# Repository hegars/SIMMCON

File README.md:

# SIMMCON
 
A KiCAD Redraw of the AWE64 SIMMConn Module from https://simmconn.tripod.com/

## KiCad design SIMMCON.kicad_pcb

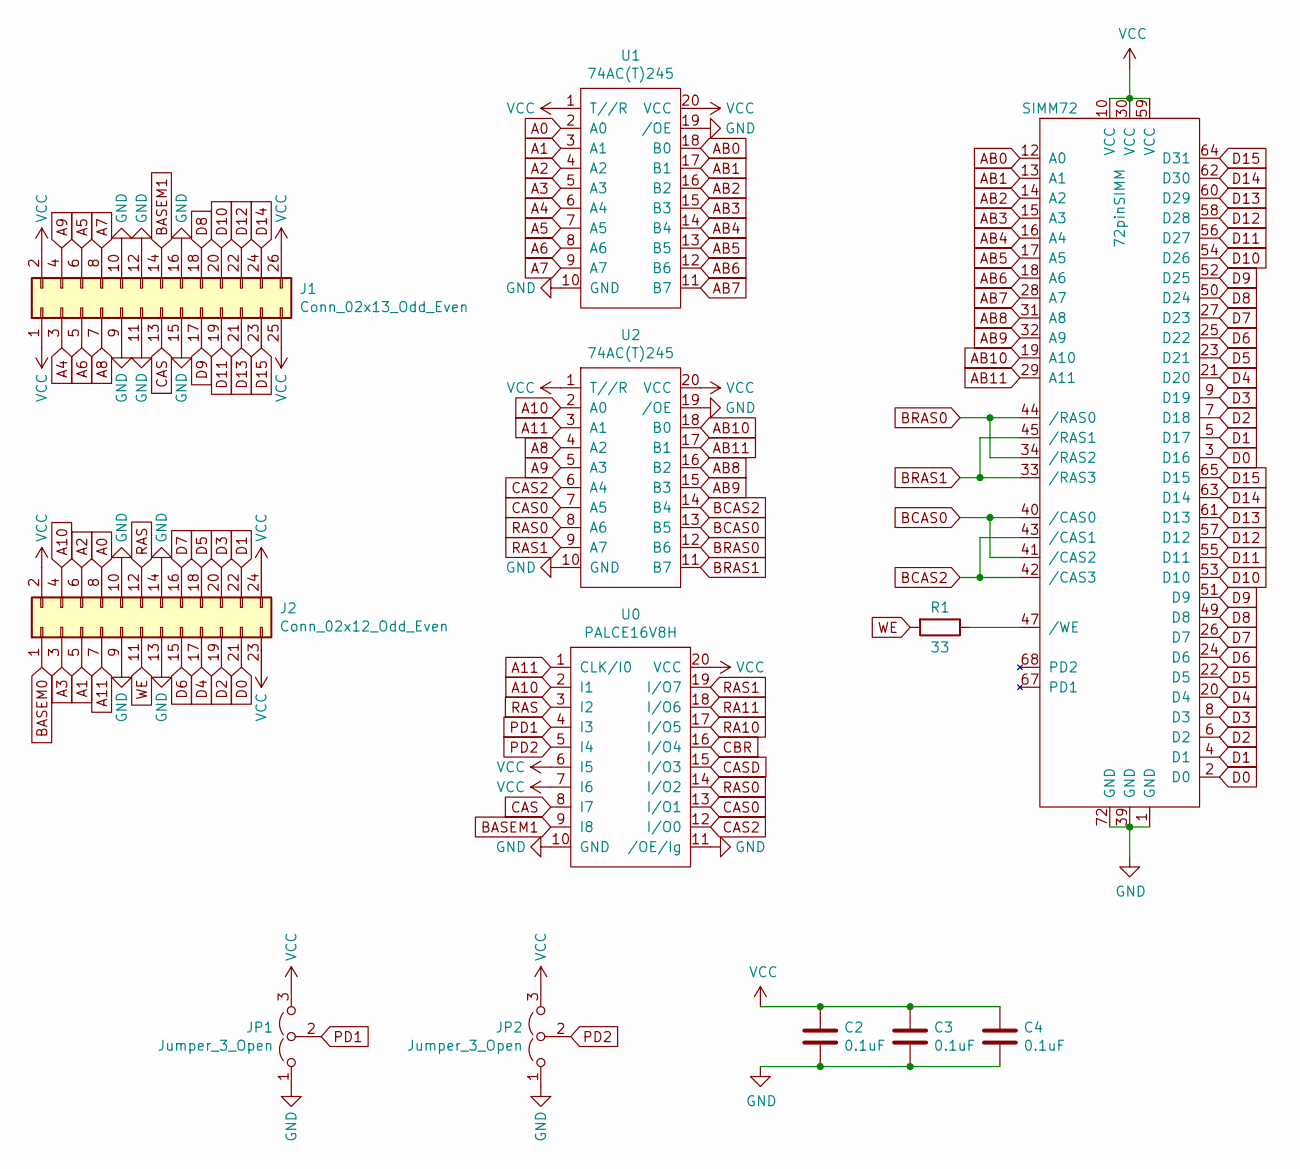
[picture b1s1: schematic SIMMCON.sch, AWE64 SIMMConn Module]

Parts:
C2, C3, C4: 0.1uF; C_0805
J1: Conn_02x13_Odd_Even; Pin_Header_Straight_2x13_Pitch2.00mm
J2: Conn_02x12_Odd_Even; Pin_Header_Straight_2x12_Pitch2.00mm
JP1, JP2: Jumper_3_Open; Pin_Header_Straight_1x03_Pitch2.54mm
R1: 33; R_0805
SIMM72: 72pinSIMM; SIM72
U0: PALCE16V8H; PLCC-20_SMD-Socket
U1, U2: 74AC(T)245; SOIC-20W_7.5x12.8mm_Pitch1.27mm

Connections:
A0: J2.8, U1.2 (A0)
A1: J2.5, U1.3 (A1)
A2: J2.6, U1.4 (A2)
A3: J2.3, U1.5 (A3)
A4: J1.3, U1.6 (A4)
A5: J1.6, U1.7 (A5)
A6: J1.5, U1.8 (A6)
A7: J1.8, U1.9 (A7)
A8: J1.7, U2.4 (A2)
A9: J1.4, U2.5 (A3)
A10: J2.4, U0.2 (I1), U2.2 (A0)
A11: J2.7, U0.1 (CLK/I0), U2.3 (A1)
AB0: SIMM72.12 (A0), U1.18 (B0)
AB1: SIMM72.13 (A1), U1.17 (B1)
AB2: SIMM72.14 (A2), U1.16 (B2)
AB3: SIMM72.15 (A3), U1.15 (B3)
AB4: SIMM72.16 (A4), U1.14 (B4)
AB5: SIMM72.17 (A5), U1.13 (B5)
AB6: SIMM72.18 (A6), U1.12 (B6)
AB7: SIMM72.28 (A7), U1.11 (B7)
AB8: SIMM72.31 (A8), U2.16 (B2)
AB9: SIMM72.32 (A9), U2.15 (B3)
AB10: SIMM72.19 (A10), U2.18 (B0)
AB11: SIMM72.29 (A11), U2.17 (B1)
BASEM0: J2.1
BASEM1: J1.14, U0.9 (I8)
BCAS0: SIMM72.40 (/CAS0), SIMM72.41 (/CAS2), U2.13 (B5)
BCAS2: SIMM72.42 (/CAS3), SIMM72.43 (/CAS1), U2.14 (B4)
BRAS0: SIMM72.34 (/RAS2), SIMM72.44 (/RAS0), U2.12 (B6)
BRAS1: SIMM72.33 (/RAS3), SIMM72.45 (/RAS1), U2.11 (B7)
CAS: J1.13, U0.8 (I7)
CAS0: U0.13 (I/O1), U2.7 (A5)
CAS2: U0.12 (I/O0), U2.6 (A4)
CASD: U0.15 (I/O3)
CBR: U0.16 (I/O4)
D0: J2.21, SIMM72.2 (D0), SIMM72.3 (D16)
D1: J2.22, SIMM72.4 (D1), SIMM72.5 (D17)
D2: J2.19, SIMM72.6 (D2), SIMM72.7 (D18)
D3: J2.20, SIMM72.8 (D3), SIMM72.9 (D19)
D4: J2.17, SIMM72.20 (D4), SIMM72.21 (D20)
D5: J2.18, SIMM72.22 (D5), SIMM72.23 (D21)
D6: J2.15, SIMM72.24 (D6), SIMM72.25 (D22)
D7: J2.16, SIMM72.26 (D7), SIMM72.27 (D23)
D8: J1.18, SIMM72.49 (D8), SIMM72.50 (D24)
D9: J1.17, SIMM72.51 (D9), SIMM72.52 (D25)
D10: J1.20, SIMM72.53 (D10), SIMM72.54 (D26)
D11: J1.19, SIMM72.55 (D11), SIMM72.56 (D27)
D12: J1.22, SIMM72.57 (D12), SIMM72.58 (D28)
D13: J1.21, SIMM72.60 (D29), SIMM72.61 (D13)
D14: J1.24, SIMM72.62 (D30), SIMM72.63 (D14)
D15: J1.23, SIMM72.64 (D31), SIMM72.65 (D15)
GND: C2.2, C3.2, C4.2, J1.9, J1.10, J1.11, J1.12, J1.15, J1.16, J2.9, J2.10, J2.13, J2.14, JP1.1 (A), JP2.1 (A), SIMM72.1 (GND), SIMM72.39 (GND), SIMM72.72 (GND), U0.10 (GND), U0.11 (/OE/Ig), U1.10 (GND), U1.19 (/OE), U2.10 (GND), U2.19 (/OE)
unnamed: R1.1, SIMM72.47 (/WE)
PD1: JP1.2 (C), U0.4 (I3)
PD2: JP2.2 (C), U0.5 (I4)
RA10: U0.17 (I/O5)
RA11: U0.18 (I/O6)
RAS: J2.12, U0.3 (I2)
RAS0: U0.14 (I/O2), U2.8 (A6)
RAS1: U0.19 (I/O7), U2.9 (A7)
VCC: C2.1, C3.1, C4.1, J1.1, J1.2, J1.25, J1.26, J2.2, J2.23, J2.24, JP1.3 (B), JP2.3 (B), SIMM72.10 (VCC), SIMM72.30 (VCC), SIMM72.59 (VCC), U0.6 (I5), U0.7 (I6), U0.20 (VCC), U1.1 (T//R), U1.20 (VCC), U2.1 (T//R), U2.20 (VCC)
WE: J2.11, R1.2

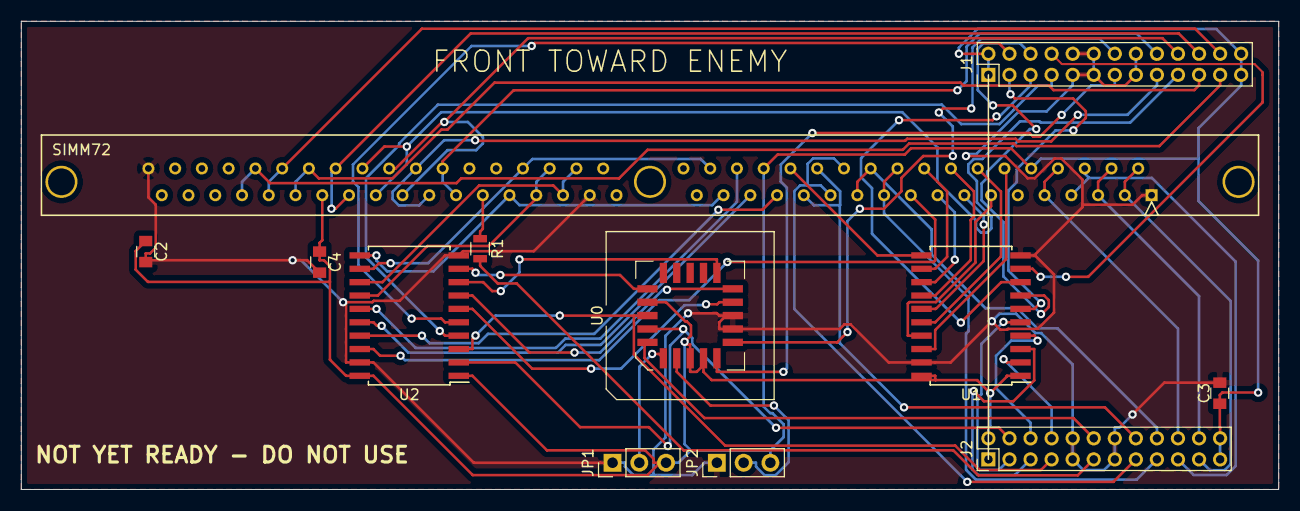
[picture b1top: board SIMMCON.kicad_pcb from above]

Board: 2 copper layers, 119.4 x 44.4 mm, 12 parts (0 on the bottom side), 57 nets.

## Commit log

2021-01-16 pdfing some stuff
2021-01-16 update some parts to soic
2021-01-17 added creative datasheets
